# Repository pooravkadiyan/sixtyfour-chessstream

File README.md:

# ChessStream India 🇮🇳♟️

**Low-cost electronic chess boards for tournament streaming in India**

## Overview

ChessStream India is an open-source project to manufacture affordable electronic chess boards (<₹2,000) for live tournament streaming. We aim to democratize chess broadcasting in India by providing tournament organizers with a cost-effective alternative to expensive DGT boards (₹36,000+).

## Why This Project?

- **570+ FIDE-rated tournaments** happen in India every year
- **DGT boards cost ₹36,000+** — prohibitive for most organizers
- **DGT's core patent (US6168158B1) expired in 2013** — no legal barriers
- **Open-source designs exist** (ChessTrace, LiBoard) — we can build on them

## Target Specifications

| Spec | Target |
|------|--------|
| BOM Cost | <₹2,000 |
| Connectivity | WiFi (ESP32) |
| Sensing | Reed switches + magnets |
| Power | USB-C (5V) |
| Streaming | LiveChess-compatible / Lichess Board API |
| Piece Detection | Occupancy only (software infers moves) |

## Project Structure

```
├── hardware/           # PCB designs, schematics, enclosure CAD
│   ├── pcb/           # KiCad project files
│   ├── enclosure/     # 3D printable / laser-cut designs
│   └── bom/           # Bill of Materials
├── firmware/          # ESP32 firmware (Arduino/PlatformIO)
│   ├── src/           # Main source code
│   └── lib/           # Libraries
├── software/          # Desktop/web streaming software
│   ├── server/        # Local relay server
│   └── web/           # Web dashboard
├── docs/              # Documentation
│   ├── assembly/      # Assembly instructions
│   ├── api/           # API documentation
│   └── guides/        # User guides
└── RESEARCH_REPORT.md # Market research
```

## Hardware Design

### Sensing Technology: Reed Switches

We use **reed switches** (simplest, cheapest method):
- 64 reed switches (one per square)
- 32 neodymium magnets (one per piece)
- Binary detection: occupied/empty
- Software infers piece type from game state

### Core Components

| Component | Qty | Est. Cost |
|-----------|-----|-----------|
| ESP32-WROOM-32E | 1 | ₹125 |
| Reed switches (glass) | 64 | ₹270 |
| Neodymium magnets (10mm) | 32 | ₹135 |
| CD74HC4067 multiplexer | 4 | ₹100 |
| Custom PCB | 1 | ₹170 |
| MDF/Acrylic enclosure | 1 | ₹170 |
| Chess pieces (plastic) | 32 | ₹250 |
| USB-C connector | 1 | ₹30 |
| Passive components | lot | ₹50 |
| **Total** | | **~₹1,300** |

### Schematic Overview

```
                    ┌─────────────────┐
                    │     ESP32       │
                    │   (WiFi MCU)    │
                    └────────┬────────┘
                             │
         ┌───────────────────┼───────────────────┐
         │                   │                   │
    ┌────┴────┐        ┌────┴────┐        ┌────┴────┐
    │  MUX 1  │        │  MUX 2  │   ...  │  MUX 4  │
    │(16 ch)  │        │(16 ch)  │        │(16 ch)  │
    └────┬────┘        └────┬────┘        └────┬────┘
         │                   │                   │
    ┌────┴────┐        ┌────┴────┐        ┌────┴────┐
    │ Reed    │        │ Reed    │        │ Reed    │
    │Switches │        │Switches │        │Switches │
    │ (a1-h2) │        │ (a3-h4) │        │ (a7-h8) │
    └─────────┘        └─────────┘        └─────────┘
```

## Firmware

The ESP32 firmware:
1. Scans all 64 reed switches via multiplexers
2. Detects piece movements (lift/place events)
3. Maintains board state
4. Broadcasts moves via WebSocket/MQTT
5. Supports LiveChess protocol for compatibility

### Key Features
- **Debouncing**: Handles noisy reed switch signals
- **Move validation**: Basic chess rule validation
- **Offline buffer**: Stores moves if WiFi drops
- **OTA updates**: Over-the-air firmware updates

## Software

### Streaming Server
- Local relay server (Python/Node.js)
- Connects to multiple boards
- Broadcasts to Chess.com/Lichess/custom platforms
- PGN export and game archival

### Web Dashboard
- Real-time board visualization
- Tournament management
- Multi-board monitoring
- Player/game metadata entry

## Digital twin

The browser twin loads the enclosure and piece STL files and speaks the same WebSocket events as the ESP32 firmware (`lift`, `place`, `move` with UCI).

```bash
cd software/digital-twin
python -m http.server 8765
```

Open http://127.0.0.1:8765 and drag a piece. The 8×8 grid is the reed-matrix view (occupied or empty). Connect `ws://<board-ip>:81` to follow a real board, or `ws://127.0.0.1:8080/ws` to follow the Python relay.

KiCad, FreeCAD, Gerber, and LTspice sources are under `hardware/`. See `hardware/README.md`.

## Digital Twin

The browser twin loads the enclosure and piece STL files and speaks the same WebSocket events as the ESP32 firmware (`lift`, `place`, `move` with UCI).

```bash
cd software/digital-twin
python -m http.server 8765
```

Open http://127.0.0.1:8765 and drag a piece. The 8×8 grid is the reed-matrix view (occupied or empty). Connect `ws://<board-ip>:81` to follow a real board, or `ws://127.0.0.1:8080/ws` to follow the Python relay.

KiCad, FreeCAD, Gerber, and LTspice sources are under `hardware/`. See `hardware/README.md`.

## Getting Started

### Prerequisites
- ESP32 development board (for prototyping)
- Arduino IDE or PlatformIO
- Basic soldering equipment
- 3D printer or laser cutter (for enclosure)

### Quick Start

```bash
# Clone the repo
git clone https://github.com/monara-ventures/chessstream-india.git
cd chessstream-india

# Install PlatformIO (if not installed)
pip install platformio

# Build and upload firmware
cd firmware
pio run -t upload

# Start the streaming server
cd ../software/server
pip install -r requirements.txt
python server.py
```

## Roadmap

### Phase 1: Prototype (Current)
- [ ] Finalize PCB schematic
- [ ] Order prototype PCBs from JLCPCB
- [ ] Design 3D-printable enclosure
- [ ] Basic ESP32 firmware
- [ ] Simple WebSocket streaming

### Phase 2: Software
- [ ] LiveChess protocol implementation
- [ ] Lichess Board API integration
- [ ] Web dashboard MVP
- [ ] Multi-board support

### Phase 3: Production
- [ ] Optimize BOM for cost
- [ ] Design injection-molded enclosure
- [ ] Reliability testing
- [ ] Documentation

### Phase 4: Pilot
- [ ] Partner with TNSCA/MCA for pilot tournament
- [ ] Gather feedback
- [ ] Iterate on design

## Contributing

We welcome contributions! See [CONTRIBUTING.md](docs/CONTRIBUTING.md) for guidelines.

### Areas We Need Help
- **Hardware**: PCB design, enclosure design
- **Firmware**: ESP32 programming, protocol implementation
- **Software**: Web development, streaming integrations
- **Testing**: Tournament organizers willing to pilot

## References

- [ChessTrace](https://github.com/anujjainbatu/chess-trace) - Open-source ESP32 chess board
- [LiBoard](https://github.com/nicvagn/LiBoard) - Lichess-compatible board
- [DGT Patent (Expired)](https://patents.google.com/patent/US6168158B1/en)
- [Lichess Board API](https://lichess.org/api#tag/Board)

## License

This project is licensed under the MIT License - see [LICENSE](LICENSE) for details.

## Contact

**Monara Ventures**  
Poorav Kadiyan  
Email: poorav.pepi@gmail.com

---

*Made with ♟️ in India*

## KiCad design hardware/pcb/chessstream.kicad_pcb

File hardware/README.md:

# Hardware Design Documentation

## Overview

The ChessStream board uses a simple but effective sensing approach:
- **64 reed switches** arranged in an 8x8 grid (one per square)
- **4 multiplexers** (CD74HC4067) to read all switches with minimal GPIO
- **ESP32** microcontroller for WiFi connectivity and processing
- **Neodymium magnets** embedded in chess piece bases

## Schematic

### Block Diagram

```
┌─────────────────────────────────────────────────────────────────┐
│                         CHESS BOARD                              │
│  ┌─────────────────────────────────────────────────────────┐    │
│  │                    8x8 Reed Switch Matrix                │    │
│  │   a8  b8  c8  d8  e8  f8  g8  h8                        │    │
│  │   ○   ○   ○   ○   ○   ○   ○   ○   ← Row 8              │    │
│  │   a7  b7  c7  d7  e7  f7  g7  h7                        │    │
│  │   ○   ○   ○   ○   ○   ○   ○   ○   ← Row 7              │    │
│  │   ...                                                    │    │
│  │   a1  b1  c1  d1  e1  f1  g1  h1                        │    │
│  │   ○   ○   ○   ○   ○   ○   ○   ○   ← Row 1              │    │
│  └─────────────────────────────────────────────────────────┘    │
│                              │                                   │
│                              ▼                                   │
│  ┌─────────┐ ┌─────────┐ ┌─────────┐ ┌─────────┐               │
│  │  MUX 1  │ │  MUX 2  │ │  MUX 3  │ │  MUX 4  │               │
│  │ (a1-h2) │ │ (a3-h4) │ │ (a5-h6) │ │ (a7-h8) │               │
│  │CD74HC   │ │CD74HC   │ │CD74HC   │ │CD74HC   │               │
│  │  4067   │ │  4067   │ │  4067   │ │  4067   │               │
│  └────┬────┘ └────┬────┘ └────┬────┘ └────┬────┘               │
│       │           │           │           │                     │
│       └───────────┴─────┬─────┴───────────┘                     │
│                         │                                        │
│                         ▼                                        │
│              ┌─────────────────────┐                            │
│              │       ESP32         │                            │
│              │   ┌─────────────┐   │                            │
│              │   │   WiFi      │   │◄──── 2.4GHz Antenna        │
│              │   └─────────────┘   │                            │
│              │   GPIO 32-35 (MUX)  │                            │
│              │   GPIO 25-28 (SEL)  │                            │
│              └──────────┬──────────┘                            │
│                         │                                        │
│                    USB-C (5V)                                    │
└─────────────────────────────────────────────────────────────────┘
```

### Pin Mapping

#### ESP32 GPIO Assignments

| GPIO | Function | Description |
|------|----------|-------------|
| 32 | MUX1_SIG | Multiplexer 1 signal output |
| 33 | MUX2_SIG | Multiplexer 2 signal output |
| 34 | MUX3_SIG | Multiplexer 3 signal output |
| 35 | MUX4_SIG | Multiplexer 4 signal output |
| 25 | SEL_A | Multiplexer select bit 0 |
| 26 | SEL_B | Multiplexer select bit 1 |
| 27 | SEL_C | Multiplexer select bit 2 |
| 14 | SEL_D | Multiplexer select bit 3 |
| 2 | LED | Status LED |

#### Multiplexer Channel Mapping

Each CD74HC4067 has 16 channels (0-15). We map them to squares:

**MUX 1 (Rows 1-2):**
| Channel | Square | Channel | Square |
|---------|--------|---------|--------|
| 0 | a1 | 8 | a2 |
| 1 | b1 | 9 | b2 |
| 2 | c1 | 10 | c2 |
| 3 | d1 | 11 | d2 |
| 4 | e1 | 12 | e2 |
| 5 | f1 | 13 | f2 |
| 6 | g1 | 14 | g2 |
| 7 | h1 | 15 | h2 |

**MUX 2 (Rows 3-4):** Same pattern for a3-h4  
**MUX 3 (Rows 5-6):** Same pattern for a5-h6  
**MUX 4 (Rows 7-8):** Same pattern for a7-h8

### Reed Switch Circuit

Each reed switch is connected with a pull-up resistor:

```
    VCC (3.3V)
        │
        ├──[10kΩ]──┬──► To MUX Channel
        │          │
        │       [Reed]
        │          │
        └──────────┴──► GND (when magnet present)
```

- **No magnet**: Reed switch OPEN → GPIO reads HIGH (1)
- **Magnet present**: Reed switch CLOSED → GPIO reads LOW (0)

### Power Supply

```
USB-C (5V) ──► AMS1117-3.3 ──► 3.3V Rail
                    │
                    ├──► ESP32 (3.3V)
                    ├──► Multiplexers (3.3V)
                    └──► Pull-up resistors
```

- Input: 5V via USB-C
- Regulated: 3.3V via AMS1117-3.3
- Current draw: ~150mA typical, ~300mA peak (WiFi TX)

## PCB Design

### Layer Stack-up

2-layer PCB:
- **Top**: Components, signal traces
- **Bottom**: Ground plane, power traces

### Design Rules

| Parameter | Value |
|-----------|-------|
| Trace width (signal) | 0.25mm |
| Trace width (power) | 0.5mm |
| Clearance | 0.2mm |
| Via size | 0.8mm/0.4mm |
| Board thickness | 1.6mm |

### PCB Dimensions

- **Main board**: 450mm x 450mm (standard tournament size)
- **Controller board**: 80mm x 50mm (separate, connects via ribbon cable)

## Bill of Materials (BOM)

### Electronics

| Ref | Component | Qty | Unit Cost | Total | Supplier |
|-----|-----------|-----|-----------|-------|----------|
| U1 | ESP32-WROOM-32E | 1 | ₹125 | ₹125 | AliExpress |
| U2-U5 | CD74HC4067 | 4 | ₹25 | ₹100 | AliExpress |
| U6 | AMS1117-3.3 | 1 | ₹5 | ₹5 | AliExpress |
| SW1-SW64 | Reed switch (glass) | 64 | ₹4 | ₹256 | AliExpress |
| R1-R64 | 10kΩ 0805 | 64 | ₹0.50 | ₹32 | AliExpress |
| C1-C6 | 100nF 0805 | 6 | ₹1 | ₹6 | AliExpress |
| C7-C8 | 10µF 0805 | 2 | ₹2 | ₹4 | AliExpress |
| J1 | USB-C connector | 1 | ₹15 | ₹15 | AliExpress |
| LED1 | LED 0805 (blue) | 1 | ₹1 | ₹1 | AliExpress |
| R65 | 330Ω 0805 | 1 | ₹0.50 | ₹0.50 | AliExpress |
| | **Electronics Total** | | | **₹544.50** | |

### Mechanical

| Item | Qty | Unit Cost | Total | Supplier |
|------|-----|-----------|-------|----------|
| PCB (450x450mm, 2-layer) | 1 | ₹300 | ₹300 | JLCPCB |
| Controller PCB (80x50mm) | 1 | ₹50 | ₹50 | JLCPCB |
| MDF board (500x500x6mm) | 1 | ₹100 | ₹100 | Local |
| Acrylic sheet (500x500x3mm) | 1 | ₹150 | ₹150 | Local |
| Vinyl squares (printed) | 1 | ₹50 | ₹50 | Local |
| Rubber feet | 4 | ₹5 | ₹20 | Local |
| Screws, standoffs | lot | ₹30 | ₹30 | Local |
| | **Mechanical Total** | | | **₹700** | |

### Chess Pieces

| Item | Qty | Unit Cost | Total | Supplier |
|------|-----|-----------|-------|----------|
| Plastic chess pieces (tournament) | 1 set | ₹150 | ₹150 | Local |
| Neodymium magnets (10x3mm) | 32 | ₹4 | ₹128 | AliExpress |
| | **Pieces Total** | | | **₹278** | |

### Total BOM

| Category | Cost |
|----------|------|
| Electronics | ₹544.50 |
| Mechanical | ₹700 |
| Chess Pieces | ₹278 |
| **Grand Total** | **₹1,522.50** |

*Note: Prices at 100+ unit volume. Prototype costs will be higher.*

## Assembly Instructions

See [docs/assembly/ASSEMBLY.md](../assembly/ASSEMBLY.md) for step-by-step instructions.

## Design Files

Open `pcb/chessstream.kicad_pro` in KiCad 8. The root sheet links `controller.kicad_sch` (ESP32, USB-C, AMS1117) and `reed_matrix.kicad_sch` (64 reeds, four CD74HC4067). Global labels `3V3`, `GND`, `SIG1`–`SIG4`, `S0`–`S3`, and `LED` tie the sheets together. Muxes are on the 450 mm board; the 80×50 mm controller is `controller.kicad_pcb`.

- `pcb/chessstream.kicad_pcb` — 450×450 mm matrix
- `pcb/controller.kicad_pcb` — 80×50 mm controller
- `gerber/matrix/` and `gerber/controller/` — Gerber and Excellon
- `gerber/bom.csv`, `gerber/positions_matrix.csv`, `gerber/positions_controller.csv`
- `enclosure/generate_enclosure.py` — parametric FreeCAD script (square pockets, reed holes, magnet cavities)
- `enclosure/export/*.stl` — meshes used by the digital twin
- `enclosure/export/laser_cut.dxf` — laser-cut frame
- `enclosure/export/assembly.step` — major solids
- `simulation/` — LTspice decks and `RESULTS.md`

Regenerate everything with `python hardware/tools/generate_design.py`.

## References

- [ESP32 Datasheet](https://www.espressif.com/sites/default/files/documentation/esp32-wroom-32e_esp32-wroom-32ue_datasheet_en.pdf)
- [CD74HC4067 Datasheet](https://www.ti.com/lit/ds/symlink/cd74hc4067.pdf)
- [ChessTrace Hardware](https://github.com/anujjainbatu/chess-trace/tree/main/hardware)

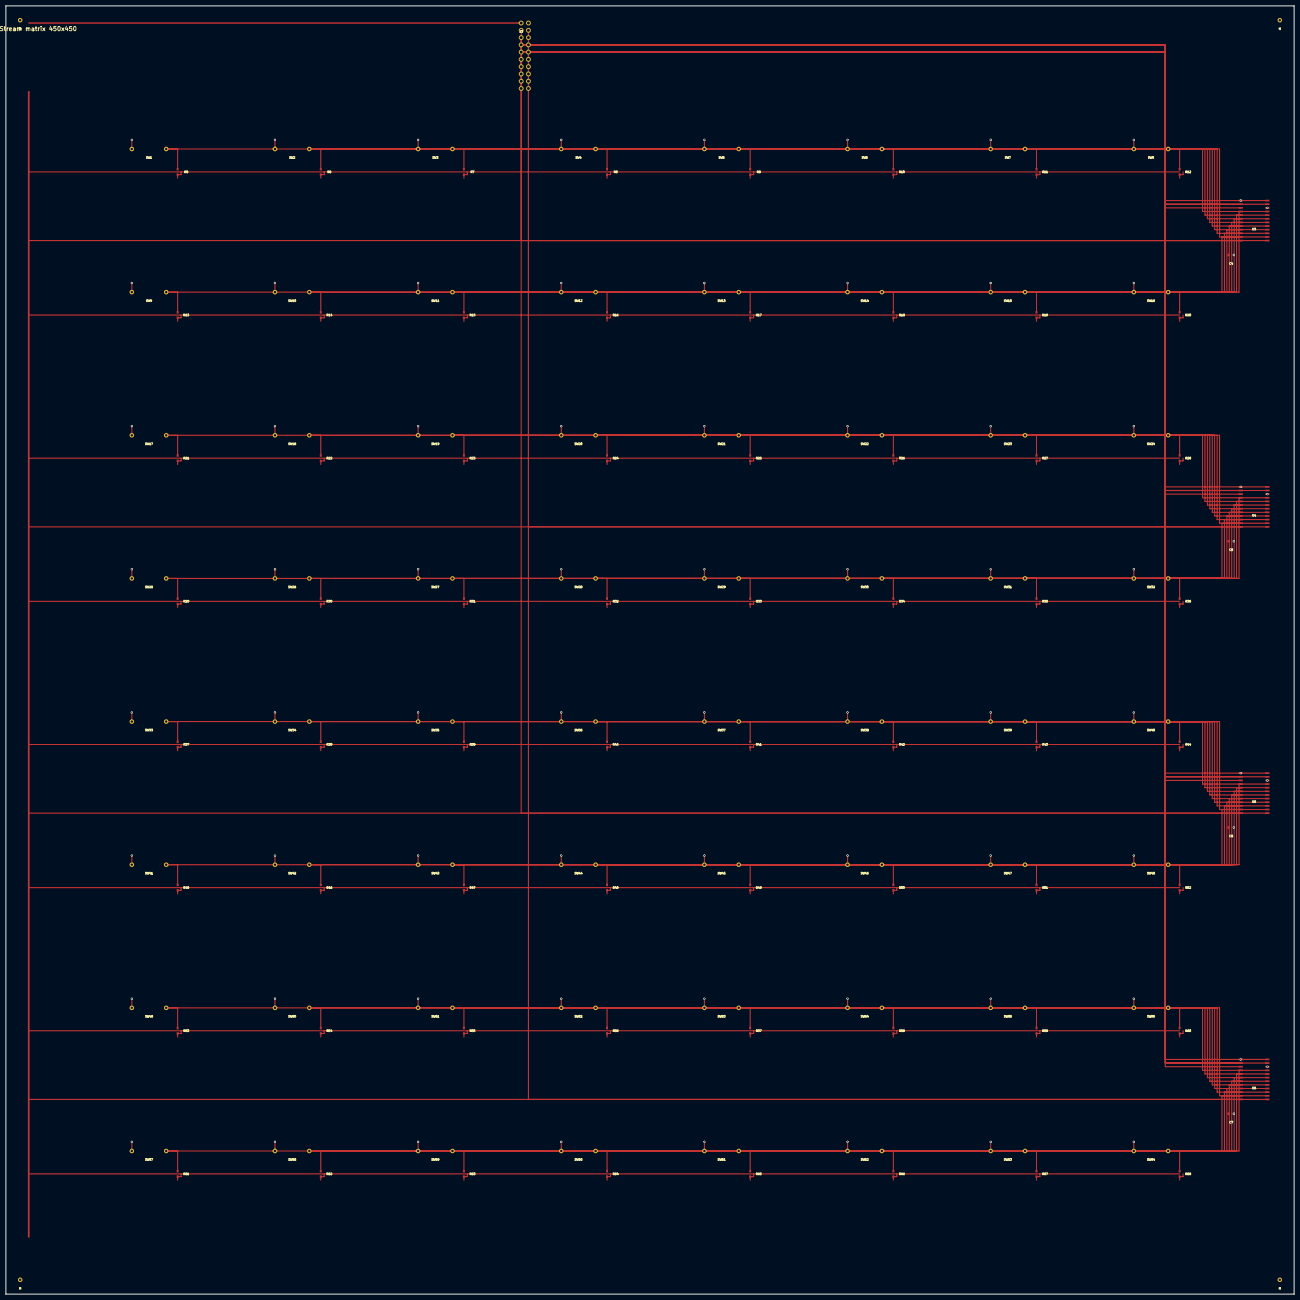
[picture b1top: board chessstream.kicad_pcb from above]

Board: 2 copper layers, 450.0 x 450.0 mm, 141 parts (0 on the bottom side), 74 nets.

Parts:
C4, C5, C6, C7: 100nF; C_0805
H: M3; MountingHole
H#2, H#3, H#4: M3; MountingHole
J3: TO_CONTROLLER; PinHeader_2x10_P2.54
R5, R6, R7, R8, R9, R10, R11, R12, R13, R14, R15, R16, R17, R18, R19, R20, R21, R22, R23, R24, R25, R26, R27, R28, R29, R30, R31, R32, R33, R34, R35, R36, R37, R38, R39, R40, R41, R42, R43, R44, R45, R46, R47, R48, R49, R50, R51, R52, R53, R54, R55, R56, R57, R58, R59, R60, R61, R62, R63, R64, R65, R66, R67, R68: 10k; R_0805
SW1: a1; ReedSwitch_D2_L12
SW2: b1; ReedSwitch_D2_L12
SW3: c1; ReedSwitch_D2_L12
SW4: d1; ReedSwitch_D2_L12
SW5: e1; ReedSwitch_D2_L12
SW6: f1; ReedSwitch_D2_L12
SW7: g1; ReedSwitch_D2_L12
SW8: h1; ReedSwitch_D2_L12
SW9: a2; ReedSwitch_D2_L12
SW10: b2; ReedSwitch_D2_L12
SW11: c2; ReedSwitch_D2_L12
SW12: d2; ReedSwitch_D2_L12
SW13: e2; ReedSwitch_D2_L12
SW14: f2; ReedSwitch_D2_L12
SW15: g2; ReedSwitch_D2_L12
SW16: h2; ReedSwitch_D2_L12
SW17: a3; ReedSwitch_D2_L12
SW18: b3; ReedSwitch_D2_L12
SW19: c3; ReedSwitch_D2_L12
SW20: d3; ReedSwitch_D2_L12
SW21: e3; ReedSwitch_D2_L12
SW22: f3; ReedSwitch_D2_L12
SW23: g3; ReedSwitch_D2_L12
SW24: h3; ReedSwitch_D2_L12
SW25: a4; ReedSwitch_D2_L12
SW26: b4; ReedSwitch_D2_L12
SW27: c4; ReedSwitch_D2_L12
SW28: d4; ReedSwitch_D2_L12
SW29: e4; ReedSwitch_D2_L12
SW30: f4; ReedSwitch_D2_L12
SW31: g4; ReedSwitch_D2_L12
SW32: h4; ReedSwitch_D2_L12
SW33: a5; ReedSwitch_D2_L12
SW34: b5; ReedSwitch_D2_L12
SW35: c5; ReedSwitch_D2_L12
SW36: d5; ReedSwitch_D2_L12
SW37: e5; ReedSwitch_D2_L12
SW38: f5; ReedSwitch_D2_L12
SW39: g5; ReedSwitch_D2_L12
SW40: h5; ReedSwitch_D2_L12
SW41: a6; ReedSwitch_D2_L12
SW42: b6; ReedSwitch_D2_L12
SW43: c6; ReedSwitch_D2_L12
SW44: d6; ReedSwitch_D2_L12
SW45: e6; ReedSwitch_D2_L12
SW46: f6; ReedSwitch_D2_L12
SW47: g6; ReedSwitch_D2_L12
SW48: h6; ReedSwitch_D2_L12
SW49: a7; ReedSwitch_D2_L12
SW50: b7; ReedSwitch_D2_L12
SW51: c7; ReedSwitch_D2_L12
SW52: d7; ReedSwitch_D2_L12
SW53: e7; ReedSwitch_D2_L12
SW54: f7; ReedSwitch_D2_L12
SW55: g7; ReedSwitch_D2_L12
SW56: h7; ReedSwitch_D2_L12
SW57: a8; ReedSwitch_D2_L12
SW58: b8; ReedSwitch_D2_L12
SW59: c8; ReedSwitch_D2_L12
SW60: d8; ReedSwitch_D2_L12
SW61: e8; ReedSwitch_D2_L12
SW62: f8; ReedSwitch_D2_L12
SW63: g8; ReedSwitch_D2_L12
SW64: h8; ReedSwitch_D2_L12
U3, U4, U5, U6: CD74HC4067; SOIC-24W_7.5x15.4_P1.27

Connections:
3V3: C4.1, C5.1, C6.1, C7.1, J3.1, R5.2, R6.2, R7.2, R8.2, R9.2, R10.2, R11.2, R12.2, R13.2, R14.2, R15.2, R16.2, R17.2, R18.2, R19.2, R20.2, R21.2, R22.2, R23.2, R24.2, R25.2, R26.2, R27.2, R28.2, R29.2, R30.2, R31.2, R32.2, R33.2, R34.2, R35.2, R36.2, R37.2, R38.2, R39.2, R40.2, R41.2, R42.2, R43.2, R44.2, R45.2, R46.2, R47.2, R48.2, R49.2, R50.2, R51.2, R52.2, R53.2, R54.2, R55.2, R56.2, R57.2, R58.2, R59.2, R60.2, R61.2, R62.2, R63.2, R64.2, R65.2, R66.2, R67.2, R68.2, U3.24, U4.24, U5.24, U6.24
GND: C4.2, C5.2, C6.2, C7.2, H.1, H#2.1, H#3.1, H#4.1, J3.2, J3.12, SW1.1, SW2.1, SW3.1, SW4.1, SW5.1, SW6.1, SW7.1, SW8.1, SW9.1, SW10.1, SW11.1, SW12.1, SW13.1, SW14.1, SW15.1, SW16.1, SW17.1, SW18.1, SW19.1, SW20.1, SW21.1, SW22.1, SW23.1, SW24.1, SW25.1, SW26.1, SW27.1, SW28.1, SW29.1, SW30.1, SW31.1, SW32.1, SW33.1, SW34.1, SW35.1, SW36.1, SW37.1, SW38.1, SW39.1, SW40.1, SW41.1, SW42.1, SW43.1, SW44.1, SW45.1, SW46.1, SW47.1, SW48.1, SW49.1, SW50.1, SW51.1, SW52.1, SW53.1, SW54.1, SW55.1, SW56.1, SW57.1, SW58.1, SW59.1, SW60.1, SW61.1, SW62.1, SW63.1, SW64.1, U3.12, U3.15, U4.12, U4.15, U5.12, U5.15, U6.12, U6.15
S0: J3.7, U3.10, U4.10, U5.10, U6.10
S1: J3.8, U3.11, U4.11, U5.11, U6.11
S2: J3.9, U3.14, U4.14, U5.14, U6.14
S3: J3.10, U3.13, U4.13, U5.13, U6.13
SIG1: J3.3, U3.1
SIG2: J3.4, U4.1
SIG3: J3.5, U5.1
SIG4: J3.6, U6.1
SQ_a1: R5.1, SW1.2, U3.9
SQ_a2: R13.1, SW9.2, U3.23
SQ_a3: R21.1, SW17.2, U4.9
SQ_a4: R29.1, SW25.2, U4.23
SQ_a5: R37.1, SW33.2, U5.9
SQ_a6: R45.1, SW41.2, U5.23
SQ_a7: R53.1, SW49.2, U6.9
SQ_a8: R61.1, SW57.2, U6.23
SQ_b1: R6.1, SW2.2, U3.8
SQ_b2: R14.1, SW10.2, U3.22
SQ_b3: R22.1, SW18.2, U4.8
SQ_b4: R30.1, SW26.2, U4.22
SQ_b5: R38.1, SW34.2, U5.8
SQ_b6: R46.1, SW42.2, U5.22
SQ_b7: R54.1, SW50.2, U6.8
SQ_b8: R62.1, SW58.2, U6.22
SQ_c1: R7.1, SW3.2, U3.7
SQ_c2: R15.1, SW11.2, U3.21
SQ_c3: R23.1, SW19.2, U4.7
SQ_c4: R31.1, SW27.2, U4.21
SQ_c5: R39.1, SW35.2, U5.7
SQ_c6: R47.1, SW43.2, U5.21
SQ_c7: R55.1, SW51.2, U6.7
SQ_c8: R63.1, SW59.2, U6.21
SQ_d1: R8.1, SW4.2, U3.6
SQ_d2: R16.1, SW12.2, U3.20
SQ_d3: R24.1, SW20.2, U4.6
SQ_d4: R32.1, SW28.2, U4.20
SQ_d5: R40.1, SW36.2, U5.6
SQ_d6: R48.1, SW44.2, U5.20
SQ_d7: R56.1, SW52.2, U6.6
SQ_d8: R64.1, SW60.2, U6.20
SQ_e1: R9.1, SW5.2, U3.5
SQ_e2: R17.1, SW13.2, U3.19
SQ_e3: R25.1, SW21.2, U4.5
SQ_e4: R33.1, SW29.2, U4.19
SQ_e5: R41.1, SW37.2, U5.5
SQ_e6: R49.1, SW45.2, U5.19
SQ_e7: R57.1, SW53.2, U6.5
SQ_e8: R65.1, SW61.2, U6.19
SQ_f1: R10.1, SW6.2, U3.4
SQ_f2: R18.1, SW14.2, U3.18
SQ_f3: R26.1, SW22.2, U4.4
SQ_f4: R34.1, SW30.2, U4.18
SQ_f5: R42.1, SW38.2, U5.4
SQ_f6: R50.1, SW46.2, U5.18
SQ_f7: R58.1, SW54.2, U6.4
SQ_f8: R66.1, SW62.2, U6.18
SQ_g1: R11.1, SW7.2, U3.3
SQ_g2: R19.1, SW15.2, U3.17
SQ_g3: R27.1, SW23.2, U4.3
SQ_g4: R35.1, SW31.2, U4.17
SQ_g5: R43.1, SW39.2, U5.3
SQ_g6: R51.1, SW47.2, U5.17
SQ_g7: R59.1, SW55.2, U6.3
SQ_g8: R67.1, SW63.2, U6.17
SQ_h1: R12.1, SW8.2, U3.2
SQ_h2: R20.1, SW16.2, U3.16
SQ_h3: R28.1, SW24.2, U4.2
SQ_h4: R36.1, SW32.2, U4.16
SQ_h5: R44.1, SW40.2, U5.2
SQ_h6: R52.1, SW48.2, U5.16
SQ_h7: R60.1, SW56.2, U6.2
SQ_h8: R68.1, SW64.2, U6.16

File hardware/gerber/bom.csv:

Designator,Value,Footprint,Quantity,LCSC
"C4 C5 C6 C7 C3",100nF,,5,C1525
"R5 R6 R7 R8 R9 R10 R11 R12 R13 R14 R15 R16 R17 R18 R19 R20 R21 R22 R23 R24 R25 R26 R27 R28 R29 R30 R31 R32 R33 R34 R35 R36 R37 R38 R39 R40 R41 R42 R43 R44 R45 R46 R47 R48 R49 R50 R51 R52 R53 R54 R55 R56 R57 R58 R59 R60 R61 R62 R63 R64 R65 R66 R67 R68 R3",10k,,65,C25804
"C1 C2",10uF,,2,C15850
"R4",330,,1,C23138
"R1 R2",5.1k,,2,C25905
"U1",AMS1117-3.3,,1,C6186
"D1",BLUE,,1,C2297
"U3 U4 U5 U6",CD74HC4067,,4,C514342
"U2",ESP32-WROOM-32E,,1,C701341
"J3",TO_CONTROLLER,,1,C49257
"J2",TO_MATRIX,,1,C49257
"J1",USB-C,,1,C2765186
"SW1",a1,,1,
"SW9",a2,,1,
"SW17",a3,,1,
"SW25",a4,,1,
"SW33",a5,,1,
"SW41",a6,,1,
"SW49",a7,,1,
"SW57",a8,,1,
"SW2",b1,,1,
"SW10",b2,,1,
"SW18",b3,,1,
"SW26",b4,,1,
"SW34",b5,,1,
"SW42",b6,,1,
"SW50",b7,,1,
"SW58",b8,,1,
"SW3",c1,,1,
"SW11",c2,,1,
"SW19",c3,,1,
"SW27",c4,,1,
"SW35",c5,,1,
"SW43",c6,,1,
"SW51",c7,,1,
"SW59",c8,,1,
"SW4",d1,,1,
"SW12",d2,,1,
"SW20",d3,,1,
"SW28",d4,,1,
"SW36",d5,,1,
"SW44",d6,,1,
"SW52",d7,,1,
"SW60",d8,,1,
"SW5",e1,,1,
"SW13",e2,,1,
"SW21",e3,,1,
"SW29",e4,,1,
"SW37",e5,,1,
"SW45",e6,,1,
"SW53",e7,,1,
"SW61",e8,,1,
"SW6",f1,,1,
"SW14",f2,,1,
"SW22",f3,,1,
"SW30",f4,,1,
"SW38",f5,,1,
"SW46",f6,,1,
"SW54",f7,,1,
"SW62",f8,,1,
"SW7",g1,,1,
"SW15",g2,,1,
"SW23",g3,,1,
"SW31",g4,,1,
"SW39",g5,,1,
"SW47",g6,,1,
"SW55",g7,,1,
"SW63",g8,,1,
"SW8",h1,,1,
"SW16",h2,,1,
"SW24",h3,,1,
"SW32",h4,,1,
"SW40",h5,,1,
"SW48",h6,,1,
"SW56",h7,,1,
"SW64",h8,,1,

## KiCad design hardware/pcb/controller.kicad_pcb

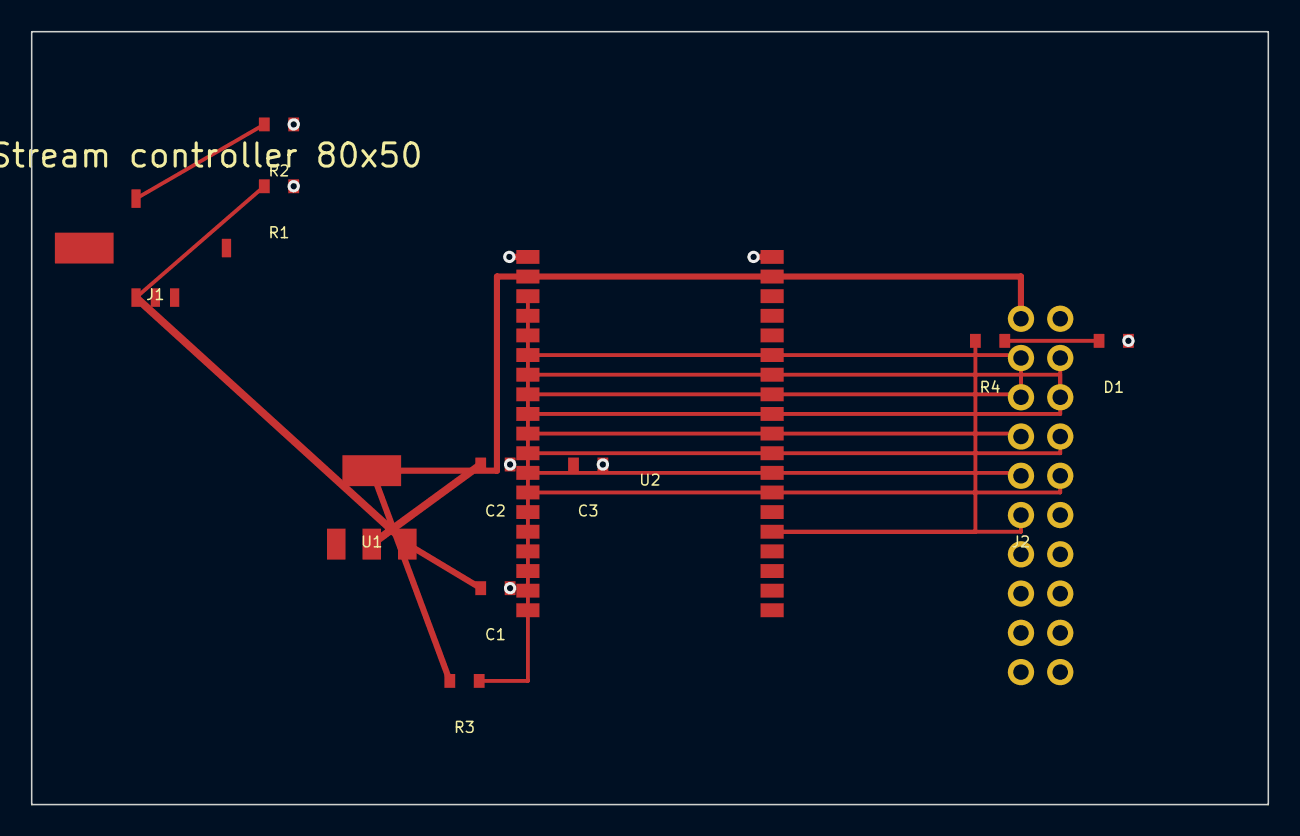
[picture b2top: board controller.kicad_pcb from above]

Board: 2 copper layers, 80.0 x 50.0 mm, 12 parts (0 on the bottom side), 16 nets.

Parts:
C1, C2: 10uF; C_0805
C3: 100nF; C_0805
D1: BLUE; LED_0805
J1: USB-C; USB_C_16_PowerOnly
J2: TO_MATRIX; PinHeader_2x10_P2.54
R1, R2: 5.1k; R_0805
R3: 10k; R_0805
R4: 330; R_0805
U1: AMS1117-3.3; SOT-223
U2: ESP32-WROOM-32E

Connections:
3V3: C2.1, C3.1, J2.1, R3.1, U1.2, U2.2
CC1: J1.A5, R1.1
CC2: J1.B5, R2.1
EN: R3.2, U2.3
GND: C1.2, C2.2, C3.2, D1.2, J1.A1, J1.SH, J2.2, J2.12, R1.2, R2.2, U1.1, U2.1, U2.38
LED: J2.11, R4.1, U2.24
LED_A: D1.1, R4.2
S0: J2.7, U2.10
S1: J2.8, U2.11
S2: J2.9, U2.12
S3: J2.10, U2.13
SIG1: J2.3, U2.8
SIG2: J2.4, U2.9
SIG3: J2.5, U2.6
SIG4: J2.6, U2.7
VBUS: C1.1, J1.A4, U1.3

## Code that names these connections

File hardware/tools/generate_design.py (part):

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    )
    note(
        root,
        "Global labels 3V3 GND SIG1-4 S0-S3 LED tie the controller to the matrix. "
        "Muxes sit on the 450mm board. The 80x50mm controller carries ESP32, USB-C and the LDO. "
        "Reed closes to GND when a magnet is present. 10k pulls each channel up to 3.3V.",
        25,
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    wire(ctrl, 250 - 3.81, 60, 242, 60)
    glabel(ctrl, "LED", 242, 60, "input")
    wire(ctrl, 250 + 3.81, 60, 258, 60)
    glabel(ctrl, "LED_A", 258, 60)

    part("chessstream:LED", "D1", "BLUE", "chessstream:LED_0805", 275, 60, ["1", "2"])
    wire(ctrl, 275 - 3.81, 60, 268, 60)
    glabel(ctrl, "LED_A", 268, 60)
    wire(ctrl, 275 + 3.81, 60, 283, 60)
    glabel(ctrl, "GND", 283, 60)

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            wire(ctrl, 320 + 7.62, y, 320 + 14, y)
            glabel(ctrl, name, 320 + 14, y)

    note(ctrl, "EN tied high via 10k. USB-C CC1/CC2 5.1k to GND advertise a default USB sink. GPIO34/35 are input-only and read SIG3/SIG4.", 30, 150)
    for name, y, shape in (
        ("3V3", 170, "input"),
        ("GND", 175, "bidirectional"),
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        mx,
        "Each square: reed to GND, 10k to 3V3, signal into CD74HC4067. "
        "Channel n on mux m is square index m*16+n in a1,b1.. order. E is tied to GND so the mux stays enabled. "
        "S0 is GPIO25 bit0. COM outputs are SIG1..SIG4 into GPIO32,33,34,35.",
        110,
        210,
    )
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

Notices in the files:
README.md:
License: MIT
